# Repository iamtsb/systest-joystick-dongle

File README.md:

# Joystick test dongle for Amiga Test Kit (Systest)

current version: v1.1

release date: 2019-07-26

### Why ?

I’m repairing lots of Amiga machines, and my (original) joystick connectors where failing after they have been swapped between all those machines. So that’s why I designed this dongle ( and ofcourse i’m a bit lazy to handle the joystick each time!)

### How does it works

This dongle simulates Up, Right, Down, Left, Button1, Button2, Button3.
There is an interval of approx. 1 second between the simulated actions of the “joystick”.

### More information

see: https://www.tsb.space/projects/systest-joystick-dongle/

download systest:  [Systest ( amiga ) from Keir Fraser](https://github.com/keirf/Amiga-Stuff) ( [download](https://drive.google.com/file/d/0B6F45EdkSMp1ZGhXMWRvOXVDd3M/view) ).

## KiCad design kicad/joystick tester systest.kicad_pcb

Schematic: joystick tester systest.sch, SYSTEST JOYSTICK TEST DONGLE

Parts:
C1: 10nF; C_0805_HandSoldering
C2: 1uF; C_0805_HandSoldering
D1: D; D_SOD-123
J1: DB9_Female; DB9F_CI
JP1: Jumper_NC_Dual; Pin_Header_Straight_1x03_Pitch1.27mm
Q1, Q2: MMBT3904; SOT-23
R1, R2: 220R; R_0805_HandSoldering
R3: 330K; R_0805_HandSoldering
R4: 56K; R_0805_HandSoldering
U1: NE555; SOIC-8_3.9x4.9mm_Pitch1.27mm
U2: 4017; SO-16-N
U3: ULN2003A; SO-16-N

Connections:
BACK: J1.2, U3.14 (O3)
BT1: J1.6, U3.12 (O5)
BT2: J1.9, Q2.3 (C)
BT3: J1.5, Q1.3 (C)
FORWARD: J1.1, U3.16 (O1)
GND: C1.2, C2.2, J1.8, Q1.2 (E), Q2.2 (E), U1.1 (GND), U2.8 (VDD), U2.13 (CKEN), U3.8 (GND)
LEFT: J1.3, U3.13 (O4)
unnamed: C1.1, U1.5 (CV)
unnamed: D1.2, U2.6 (Q7)
unnamed: JP1.1, R2.1
unnamed: JP1.2, U2.1 (Q5)
unnamed: Q1.1 (B), R1.2
unnamed: Q2.1 (B), R2.2
unnamed: R1.1, U2.5 (Q6)
unnamed: R3.1, R4.2, U1.7 (DIS)
unnamed: U1.3 (Q), U2.14 (CLK)
unnamed: U2.2 (Q1), U3.2 (I2)
unnamed: U2.3 (Q0), U3.1 (I1)
unnamed: U2.4 (Q2), U3.3 (I3)
unnamed: U2.7 (Q3), U3.4 (I4)
unnamed: U2.10 (Q4), U3.5 (I5)
RIGHT: J1.4, U3.15 (O2)
RST: D1.1, JP1.3, U2.15 (Reset)
THR: C2.1, R3.2, U1.2 (TR), U1.6 (THR)
VCC: J1.7, R4.1, U1.4 (R), U1.8 (VCC), U2.16 (VCC)

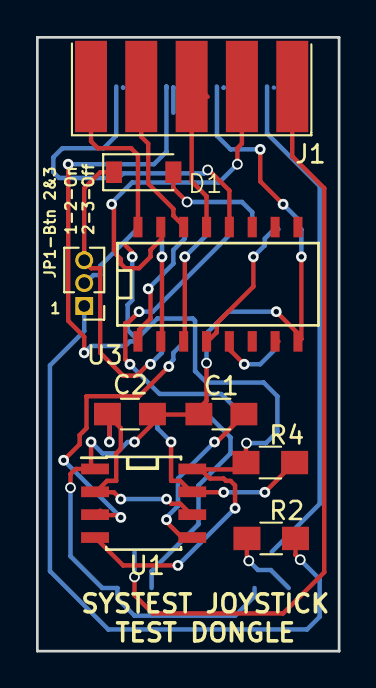
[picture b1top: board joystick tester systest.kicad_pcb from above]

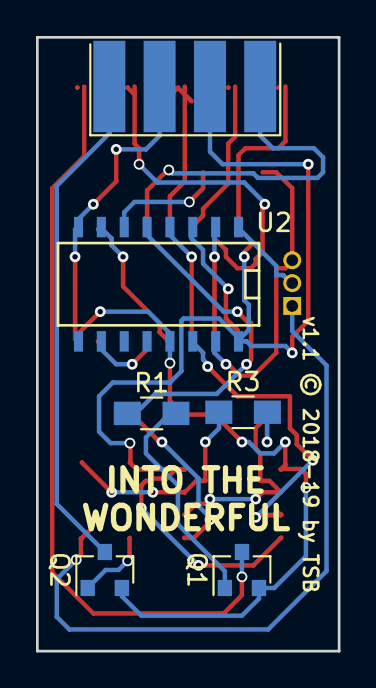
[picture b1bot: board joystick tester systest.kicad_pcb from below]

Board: 2 copper layers, 16.8 x 34.1 mm, 14 parts (5 on the bottom side), 25 nets.

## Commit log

2019-07-26 Update LICENSE
2019-07-26 init version
2019-07-26 update
    -updated pcb file with 3d models
    -added build manual

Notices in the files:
kicad/joystick tester systest.kicad_pcb:
v1.1 © 2018-19 by TSB
